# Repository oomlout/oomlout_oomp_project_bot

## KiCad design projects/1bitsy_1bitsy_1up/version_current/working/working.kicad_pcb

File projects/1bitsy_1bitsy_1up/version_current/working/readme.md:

# OOMP Project  
## 1bitsy-1up  by 1Bitsy  
  
oomp key: oomp_projects_flat_1bitsy_1bitsy_1up  
(snippet of original readme)  

This repository contains the board and code used on the 1Bitsy 1UP.  
  
-- Intro  
  
1Bitsy 1UP is a retro inspired handheld game console, the design is based  
around the following __semi arbitrary constraints and requirements.__  
  
* Formfactor: PCB the size of the inside of a GB DMG (the gray one) This will  
  hopefully eventually allow us to put the 1UP pcb inside a modified GB DMG  
  case, either original or new molds sold by several online stores.  
* Main CPU: All code should be able to execute on a 1Bitsy that is fitted with  
  an STM32F415RGT6. That particular chip (due to the package size) does not  
  contain external ram support or LCD display engine. Making LCD drive little  
  bit more tricky. It is a nice constraint that makes coding for the platform  
  bit more of a challenge in the style of classic conloles and 8bit computers  
  because it does not have enough memory for a full framebuffer. ("racing the  
  beam" FTW)  
* Main CPU Mounting: The board contains the 1Bitsy compatible low profile  
  socket using [SL-115-TT-19](https://www.samtec.com/products/sl-115-tt-19)  
  and [BBL-115-T-E](https://www.samtec.com/products/bbl-115-t-e) Samtec  
  connectors as well as one MillMax PogoPin spring loaded SMD connector.  
* LCD: The LCD is a 240x320 TFT display with capacitive touch  
  full source readme at [readme_src.md](readme_src.md)  
  
source repo at: [https://github.com/1Bitsy/1bitsy-1up](https://github.com/1Bitsy/1bitsy-1up)  
## Board  

## Schematic  

[schematic pdf](working_schematic.pdf)  
## Images

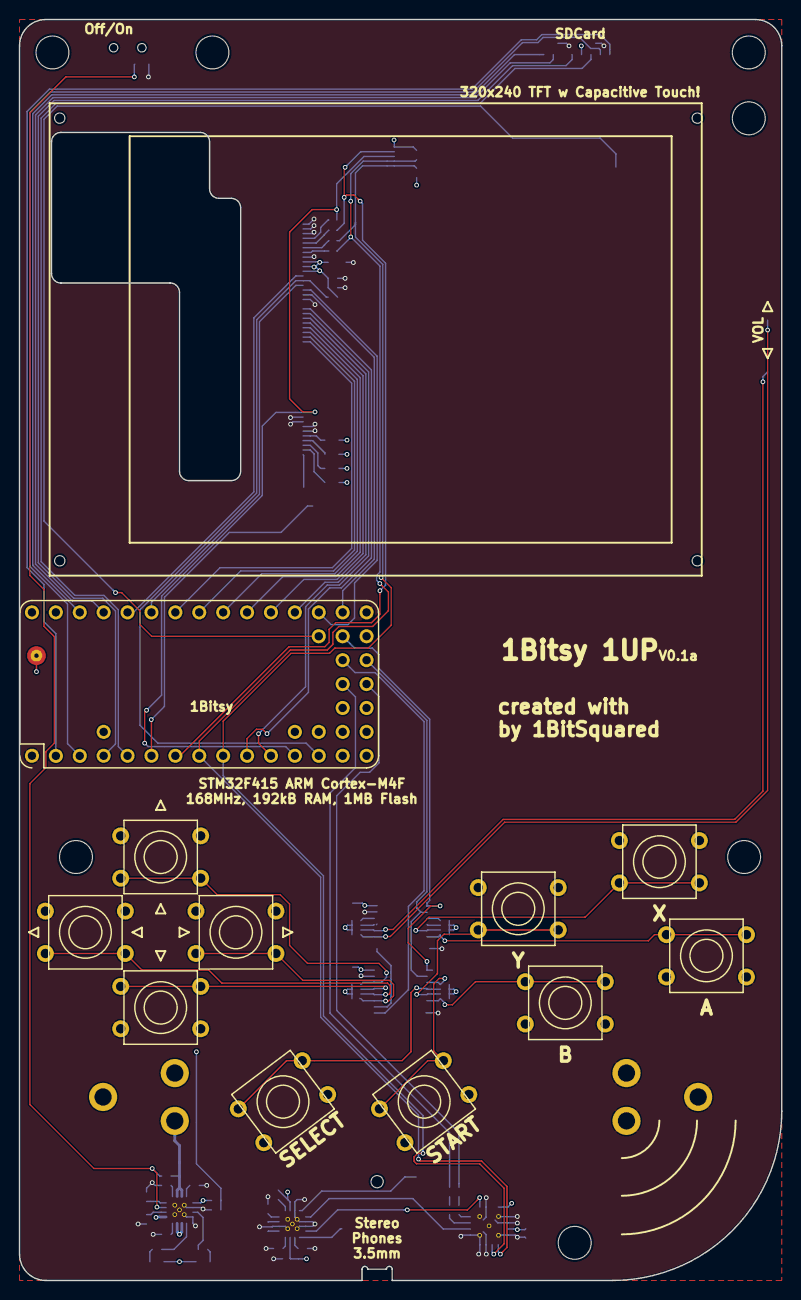
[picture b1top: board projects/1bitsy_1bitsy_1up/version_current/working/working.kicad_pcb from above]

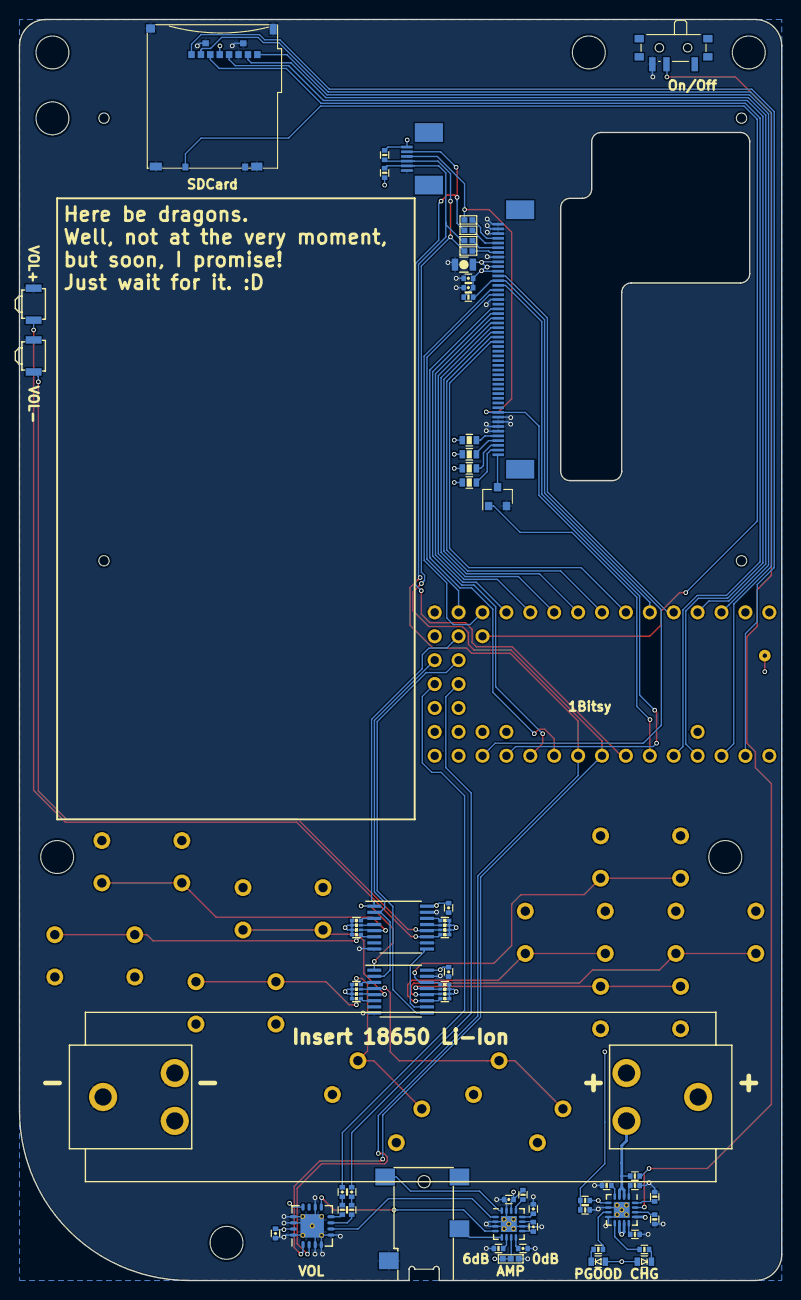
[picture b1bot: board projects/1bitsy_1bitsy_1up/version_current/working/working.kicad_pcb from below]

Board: 4 copper layers, 81.0 x 134.0 mm, 70 parts (58 on the bottom side), 86 nets.

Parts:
BT1: Battery_Cell; BATTERY_CLIP_18650
C1: 10u; C_0805
C2, C3, C10, C11, C12: 100n; C_0402
C4, C5, C6, C7, C9: 1u; C_0402
C8: 2u2; C_0402
CON1: pkl_Micro_SD; SCHA4B0419
D1: YEL; D_0603
D2: GRN; D_0603
J1, J2, J3, J4: pkl_jumper; J_0402
J6: Jumper_Dual; J_0602
J7: pkl_JACK_3C1S; SJ2-35853B-SMT
P1: PogoPin; PAD_MILL-MAX_0906
Q1: NMOS; SOT-23
R1, R2, R3, R4: 10E; R_0603
R5, R8, R9, R12, R13, R16, R17, R21, R22, R23, R25: 10k; R_0402
R6, R7, R10, R11: 10k; R_Array_Convex_4x0402
R14, R15: 50E; R_0402
R18: 0E; R_0402
R19: 590E; R_0402
R20: 1k1; R_0402
R24: 4k7; R_0402
SW1: UP; Tact_Switch_Top_TH_7.8MM_Snap
SW2: Y; Tact_Switch_Top_TH_7.8MM_Snap
SW3: LEFT; Tact_Switch_Top_TH_7.8MM_Snap
SW4: RIGHT; Tact_Switch_Top_TH_7.8MM_Snap
SW5: X; Tact_Switch_Top_TH_7.8MM_Snap
SW6: A; Tact_Switch_Top_TH_7.8MM_Snap
SW7: SELECT; Tact_Switch_Top_TH_7.8MM_Snap
SW8: DOWN; Tact_Switch_Top_TH_7.8MM_Snap
SW9: B; Tact_Switch_Top_TH_7.8MM_Snap
SW10: START; Tact_Switch_Top_TH_7.8MM_Snap
SW11: pkl_SWITCH-SPDT; SW_SPDT_PCM12
SW12, SW13: Tact_Switch_Side_B3U-3000P
U1: 1bitsy-complete-concise; 1bitsy-sl-1xx-xx-19
U2: lcd_50pin_logic; ER-CON50HT
U3: lcd_cap_touch_buydisplay; ER-CON06HB
U4, U5: 74HC165; TSSOP-16_4.4x5mm_Pitch0.65mm
U6: BQ24075; QFN-16-1EP_3x3mm_Pitch0.5mm
U7: TPA6135A2; QFN-16-1EP_3x3mm_Pitch0.5mm
U8: MCP4661-103E/ML; QFN-16-1EP_4x4mm_Pitch0.65mm

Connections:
+3V3: C1.2, C2.2, C3.2, C7.2, C10.2, C11.2, C12.2, CON1.4, J6.2, J6.3, R1.2, R2.2, R3.2, R4.2, R5.1, R6.2, R6.4, R6.6, R6.8, R7.2, R7.4, R7.6, R7.8, R8.1, R9.1, R10.2, R10.4, R10.6, R10.8, R11.2, R11.4, R11.6, R11.8, R13.1, U1.15, U1.29, U2.40, U2.41, U2.42, U3.6, U4.16, U5.16, U7.7, U7.14, U8.12, U8.15
+5V: D1.A, D2.A, R24.1, U1.30, U6.5, U6.10, U6.11
+BATT: BT1.1, R12.1, U1.14, U6.2, U6.3
/AL_AMP: J7.2, U7.16
/AL_ATT: U7.1, U8.6
/AR_AMP: J7.3, U7.5
/AR_ATT: U7.4, U8.9
/AUDIO_L: C4.1, U1.35
/AUDIO_R: C5.1, U1.36
/BA: R10.1, SW6.1, U5.6
/BB: R6.1, SW9.1, U4.6
/BCLK: U1.38, U4.2, U5.2
/BDAT: U1.37, U4.9
/BDOWN: R7.3, SW8.1, U4.13
/BLATCH: U1.39, U4.1, U5.1
/BLEFT: R7.5, SW3.1, U4.12
/BRIGHT: R7.7, SW4.1, U4.11
/BSELECT: R6.5, SW7.1, U4.4
/BSTART: R6.7, SW10.1, U4.3
/BUP: R7.1, SW1.1, U4.14
/BVol+: R11.7, SW12.1, U5.11
/BVol-: R11.5, SW13.1, U5.12
/BX: R10.3, SW5.1, U5.5
/BY: R6.3, SW2.1, U4.5
/LCD_BACK_LIGHT: Q1.1, U1.6
/LCD_BL: Q1.3, U2.1
/LCD_C/D: U1.25, U2.37
/LCD_CS: R5.2, U1.13, U2.38
/LCD_D0: U1.10, U2.32
/LCD_D1: U1.11, U2.31
/LCD_D2: U1.19, U2.30
/LCD_D3: U1.20, U2.29
/LCD_D4: U1.21, U2.28
/LCD_D5: U1.22, U2.27
/LCD_D6: U1.23, U2.26
/LCD_D7: U1.24, U2.25
/LCD_RD: U1.17, U2.35
/LCD_RST: J4.1, U1.12, U2.10, U3.4
/LCD_TE: U1.26, U2.39
/LCD_TOUCH_IRQ: J3.1, U1.7, U3.5
/LCD_WR: U1.18, U2.36
/LED1A: R1.1, U2.2
/LED2A: R2.1, U2.3
/LED3A: R3.1, U2.4
/LED4A: R4.1, U2.5
/SDIO_CD: CON1.9, U1.44
/SDIO_CK: CON1.5, U1.4
/SDIO_CMD: CON1.3, U1.5
/SDIO_D0: CON1.7, U1.27
/SDIO_D1: CON1.8, U1.28
/SDIO_D2: CON1.1, U1.2
/SDIO_D3: CON1.2, U1.3
/SYSOFF: R12.2, SW11.2, U6.15
/USB_V+: P1.1, U6.13
/VOL/TOUCH_SCL: J1.1, R9.2, U1.8, U3.3, U8.1
/VOL/TOUCH_SDA: J2.1, R8.2, U1.9, U3.2, U8.2
/V_BATT: R24.2, R25.1, U1.43
/~CHG: R16.2, U6.9
/~PGOOD: R21.2, U6.7
GND: BT1.2, C1.1, C2.1, C3.1, C7.1, C8.1, C9.1, C10.1, C11.1, C12.1, CON1.6, CON1.10, CON1.11, J6.1, J7.1, Q1.2, R17.2, R18.2, R19.2, R20.2, R22.2, R23.2, R25.2, SW1.2, SW2.2, SW3.2, SW4.2, SW5.2, SW6.2, SW7.2, SW8.2, SW9.2, SW10.2, SW11.3, SW12.2, SW13.2, U1.1, U1.16, U2.6, U2.7, U2.8, U2.9, U2.34, U2.43, U2.48, U2.49, U2.50, U3.1, U4.8, U4.15, U5.8, U5.10, U5.15, U6.6, U6.8, U6.17, U7.2, U7.3, U7.10, U7.15, U7.17, U8.3, U8.4, U8.5, U8.10, U8.13, U8.14, U8.16, U8.17
unnamed: C4.2, R14.2
unnamed: C5.2, R15.2
unnamed: C6.1, U7.9
unnamed: C6.2, U7.11
unnamed: C8.2, U7.12
unnamed: C9.2, U7.8
unnamed: D1.C, R16.1
unnamed: D2.C, R21.1
unnamed: J1.2, U2.44
unnamed: J2.2, U2.45
unnamed: J3.2, U2.46
unnamed: J4.2, U2.47
unnamed: R10.5, U5.4
unnamed: R10.7, U5.3
unnamed: R11.1, U5.14
unnamed: R11.3, U5.13
unnamed: R13.2, U7.13
unnamed: R14.1, U8.7
unnamed: R15.1, U8.8
unnamed: R17.1, U6.1
unnamed: R18.1, U6.14
unnamed: R19.1, U6.16
unnamed: R20.1, U6.12
unnamed: R22.1, U6.4
unnamed: R23.1, U7.6
unnamed: U4.10, U5.9

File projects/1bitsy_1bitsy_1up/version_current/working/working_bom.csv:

"Id";"Designator";"Footprint";"Quantity";"Designation";"Supplier and ref";
1;"R25,R5,R8,R9,R12,R13,R16,R17,R21,R22,R23";"R_0402";11;"10k";;;
2;"R24";"R_0402";1;"4k7";;;
3;"REF**,REF**,REF**,REF**,REF**,REF**,REF**";"MountingHole_3-5mm";7;"MountingHole_3-5mm";;;
4;"P1";"PAD_MILL-MAX_0906";1;"PogoPin";;;
5;"J6";"J_0602";1;"Jumper_Dual";;;
6;"U5,U4";"TSSOP-16_4.4x5mm_Pitch0.65mm";2;"74HC165";;;
7;"U1";"1bitsy-sl-1xx-xx-19";1;"1bitsy-complete-concise";;;
8;"C2,C3,C10,C11,C12";"C_0402";5;"100n";;;
9;"C4,C5,C6,C7,C9";"C_0402";5;"1u";;;
10;"C8";"C_0402";1;"2u2";;;
11;"D1";"D_0603";1;"YEL";;;
12;"D2";"D_0603";1;"GRN";;;
13;"J1,J2,J3,J4";"J_0402";4;"pkl_jumper";;;
14;"Q1";"SOT-23";1;"NMOS";;;
15;"R1,R2,R3,R4";"R_0603";4;"10E";;;
16;"R6,R7,R10,R11";"R_Array_Convex_4x0402";4;"10k";;;
17;"R14,R15";"R_0402";2;"50E";;;
18;"R18";"R_0402";1;"0E";;;
19;"R19";"R_0402";1;"590E";;;
20;"R20";"R_0402";1;"1k1";;;
21;"SW1";"Tact_Switch_Top_TH_7.8MM_Snap";1;"UP";;;
22;"SW2";"Tact_Switch_Top_TH_7.8MM_Snap";1;"Y";;;
23;"SW3";"Tact_Switch_Top_TH_7.8MM_Snap";1;"LEFT";;;
24;"SW4";"Tact_Switch_Top_TH_7.8MM_Snap";1;"RIGHT";;;
25;"SW5";"Tact_Switch_Top_TH_7.8MM_Snap";1;"X";;;
26;"SW6";"Tact_Switch_Top_TH_7.8MM_Snap";1;"A";;;
27;"SW7";"Tact_Switch_Top_TH_7.8MM_Snap";1;"SELECT";;;
28;"SW8";"Tact_Switch_Top_TH_7.8MM_Snap";1;"DOWN";;;
29;"SW9";"Tact_Switch_Top_TH_7.8MM_Snap";1;"B";;;
30;"SW10";"Tact_Switch_Top_TH_7.8MM_Snap";1;"START";;;
31;"SW11";"SW_SPDT_PCM12";1;"pkl_SWITCH-SPDT";;;
32;"SW12,SW13";"Tact_Switch_Side_B3U-3000P";2;"~";;;
33;"U2";"ER-CON50HT";1;"lcd_50pin_logic";;;
34;"U3";"ER-CON06HB";1;"lcd_cap_touch_buydisplay";;;
35;"REF**";"ER-TFT028-4-mechanical";1;"ER-TFT028-4-mechanical";;;
36;"CON1";"SCHA4B0419";1;"pkl_Micro_SD";;;
37;"BT1";"BATTERY_CLIP_18650";1;"Battery_Cell";;;
38;"J7";"SJ2-35853B-SMT";1;"pkl_JACK_3C1S";;;
39;"U7";"QFN-16-1EP_3x3mm_Pitch0.5mm";1;"TPA6135A2";;;
40;"U6";"QFN-16-1EP_3x3mm_Pitch0.5mm";1;"BQ24075";;;
41;"U8";"QFN-16-1EP_4x4mm_Pitch0.65mm";1;"MCP4661-103E/ML";;;
42;"C1";"C_0805";1;"10u";;;

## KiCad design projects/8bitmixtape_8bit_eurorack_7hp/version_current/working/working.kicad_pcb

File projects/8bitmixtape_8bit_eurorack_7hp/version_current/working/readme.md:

# OOMP Project  
## 8Bit_EuroRack-7hp  by 8BitMixtape  
  
oomp key: oomp_projects_flat_8bitmixtape_8bit_eurorack_7hp  
(snippet of original readme)  
  
- 8Bit_EuroRack-7hp  
8Bit Mixtape goes Modular!! Due to popular requests... adapted and improved the mixtape circuit to fit into standard Eurorack Modular format  
  
Join and follow our discussion on the forum:  
  
https://8bitmixtape.discourse.group/t/eurorack-rebooted/47/4  
  
- Features  
  
-- 7hp more space for style!  
  
-- Two board design  
  
Maybe the Eurorack scene like to have more this kinda standard double-decker style  
  
-- 0.1 Prototype - WORKING  

--- to improve  
  
* Put 2 Neopixel und the potentiometers each  
* switch position of Chip and Buttons to create more space between pot and buttons  
* optimize position of jacks and pots (sub-millimeter improvements)  
* What kinda buttons to use????  
* create nice front plates  
* anything else?  
  
-- Schematic  
  
  full source readme at [readme_src.md](readme_src.md)  
  
source repo at: [https://github.com/8BitMixtape/8Bit_EuroRack-7hp](https://github.com/8BitMixtape/8Bit_EuroRack-7hp)  
## Board  

## Schematic  

[schematic pdf](working_schematic.pdf)  
## Images

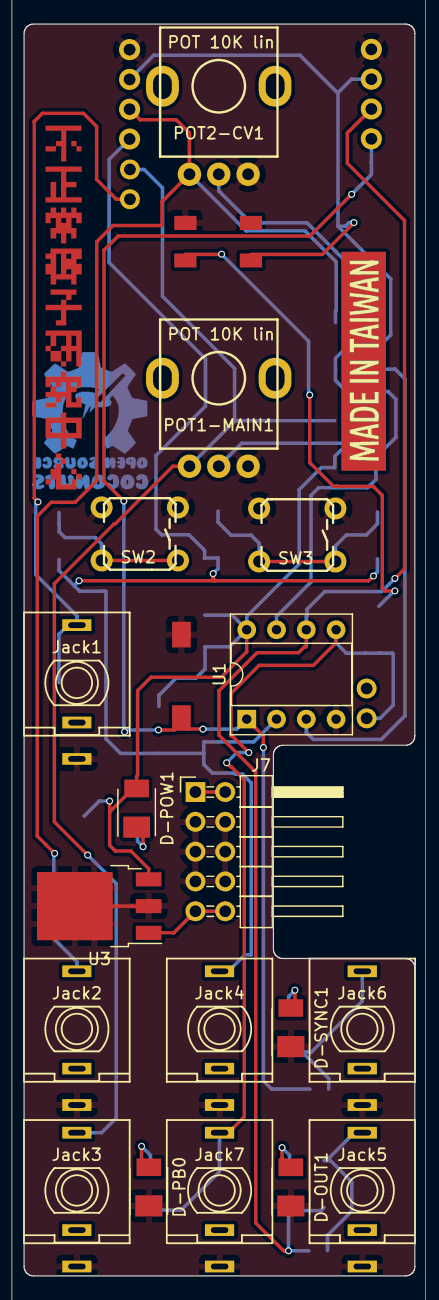
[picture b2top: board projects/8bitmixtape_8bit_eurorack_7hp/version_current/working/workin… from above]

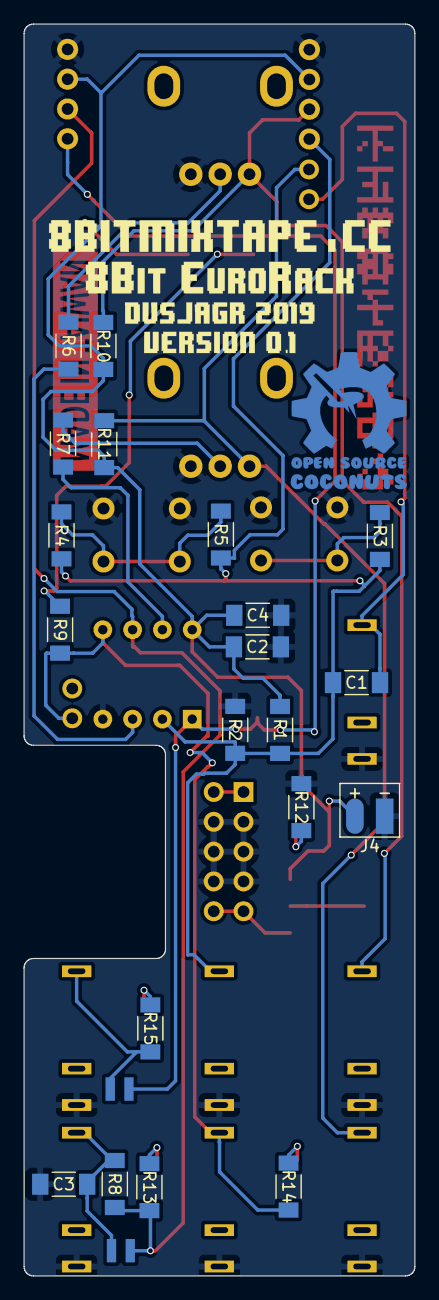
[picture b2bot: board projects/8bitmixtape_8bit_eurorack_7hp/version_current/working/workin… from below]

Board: 2 copper layers, 33.3 x 106.7 mm, 51 parts (26 on the bottom side), 24 nets.

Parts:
C1, C2, C3: 100nF; C_1206_3d
C4: 10uF; C_1206_3d
D1: SK6812; Mixtape_NEO_WS2812B_3d
D-OUT1: LED; LED_PLCC_2835_Handsoldering
D-PB0: LED; LED_PLCC_2835_Handsoldering
D-POW1: LED; LED_PLCC_2835_Handsoldering
D-SYNC1: LED; LED_PLCC_2835_Handsoldering
J1, J2: CONN_01X04; Angled_1x04_Pitch2.54mm-3d
J4: Con_3-5V; Bat_connector_SMD
J5: Conn_01x02; Socket_Strip_Angled_1x02_Pitch2.54mm
J6, J9: Sync_Jumper; Sync_jumper_small
J7: Conn_02x05_Odd_Even; Pin_Header_Angled_2x05_Pitch2.54mm_with_space_for_con
J8: Conn_01x02; Pin_Header_Angled_1x02_Pitch2.54mm
Jack1, Jack2, Jack3, Jack4, Jack5, Jack6, Jack7: JACK_2P; PJ301M-12_dusjagr_3d
POT1-MAIN1, POT2-CV1: POT 10K lin; RD901F-ALPHA-3D
R1, R2, R3, R4, R5: 22k; R_1206_3d
R6, R7: 22K; R_1206_3d
R8, R9: 330; R_1206_3d
R10, R11: 4.7K; R_1206_3d
R12, R13, R14, R15: 1K; R_1206_3d
Ref**: Val**; MadeInTaiwan
Ref**#2: Val**; CACR_chinese_vert
Ref**#3: Val**; Coconut_logo
Ref**#4: Val**; 8bitmixtape_credits_FSilk
SW2, SW3: SW_Push; TACTILE-PTH_3d
SW4: SW_Push; SW_SPST_3d
U1: ATTINY85-20SU; DIP-8_Attiny_with_Socket_3d
U3: 7805; TO-252-3_TabPin2
board1: SVG2SHENZHEN; 8Bit_EuroRack-NEO_7hp

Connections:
+3V3: C2.1, C4.1, D1.3, D-POW1.2, J1.3, J2.2, J4.2, R1.1, R10.1, R11.1, U1.8, U3.3
AudioProg: C1.1, J5.1, Jack1.1
But-L: R3.2, SW2.1
But-R: R4.2, R5.2, SW3.1
CV1_IN: J1.2, Jack2.1, POT2-CV1.1, R10.2
CV2_IN: J5.2, Jack3.1, POT1-MAIN1.1, R11.2
CV_OUT: C3.1, J9.2, Jack5.1, R8.1
DC_in: J7.9, J7.10, U3.1
GND: C2.2, C3.2, C4.2, D1.1, D-OUT1.1, D-PB0.1, D-SYNC1.1, J1.4, J2.1, J4.1, J7.3, J7.4, J7.5, J7.6, J7.7, J7.8, Jack1.3, Jack2.3, Jack3.3, Jack4.3, Jack5.3, Jack6.3, Jack7.3, POT1-MAIN1.3, POT2-CV1.3, R2.2, R12.2, SW2.2, SW3.2, SW4.2, U1.4, U3.2
unnamed: D1.2, R9.1
unnamed: D-OUT1.2, R13.2
unnamed: D-PB0.2, R14.2
unnamed: D-POW1.1, R12.1
unnamed: D-SYNC1.2, R15.2
unnamed: J7.1, J7.2
unnamed: POT1-MAIN1.2, R7.2
unnamed: POT2-CV1.2, R6.2
PB0: J8.1, Jack7.1, R9.2, R14.1, U1.5
PB1: J2.3, J9.1, R8.2, R13.1, U1.6
PB2/A1: R7.1, U1.7
PB4/A2: R6.1, U1.3
PB5: J2.4, J6.1, SW4.1, U1.1
Sync_IN: C1.2, J1.1, Jack4.1, R1.2, R2.1, R3.1, R4.1, R5.1, U1.2
Sync_OUT: J6.2, Jack6.1, R15.1

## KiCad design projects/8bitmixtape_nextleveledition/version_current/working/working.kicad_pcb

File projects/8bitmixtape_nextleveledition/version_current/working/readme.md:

# NextLevelEdition by 8BitMixtape  
This is a harvested standardized copy of a project from github.  
The original project can be found at:  
https://github.com/8BitMixtape/NextLevelEdition  
Please consult that link for additional, details, files, and license information.  
Note: It was auto harvested and if the original repo had more than one board file or anything out of the ordinary the files here are likely not representative.

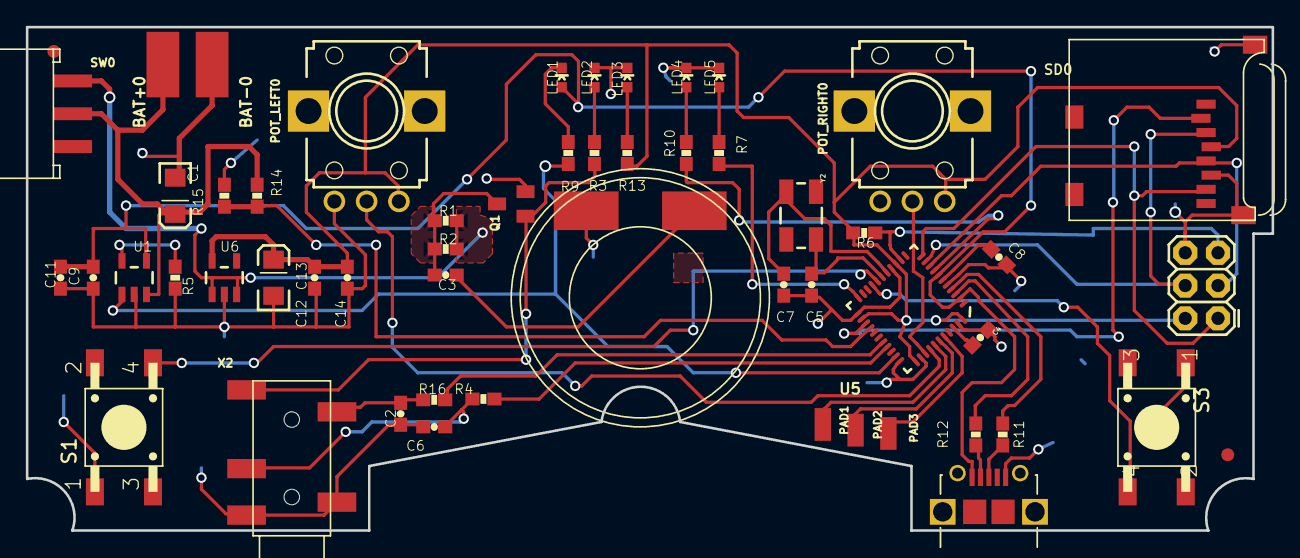
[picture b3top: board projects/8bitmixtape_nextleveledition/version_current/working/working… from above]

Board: 4 copper layers, 96.5 x 39.0 mm, 57 parts (1 on the bottom side), 42 nets.

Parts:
BAT+0: SMD2,54-5,08
BAT-0: SMD2,54-5,08
C1, C13: 10uF; EIA3216
C2, C3, C6, C8, C11, C12: 1uF; 0603-CAP
C4, C14: 0.1uF; 0603-CAP
C5, C7: 22pF; 0603-CAP
C9: 4.7uF; 0603-CAP
JP4: AVR_SPI; 2X3
LED1, LED5: Yellow; LED-0603
LED2: Blue; LED-0603
LED3: Green; LED-0603
LED4: Red; LED-0603
LOGO1: OSHW-LOGOL; OSHW-LOGO-L
PAD1, PAD2, PAD3: WIREPADSMD1,27-254; SMD1,27-2,54
POT_LEFT0: EVUF2A; EVUF
POT_RIGHT0: EVUF2A; EVUF
Q1: BSS123; SOT23
R1, R2: 33; 0603-RES
R3, R4, R7, R10, R13, R16: 330; 0603-RES
R5: 2K; 0603-RES
R6: 10K; 0603-RES
R9: 470; 0603-RES
R11, R12: 22; 0603-RES
R14, R15: 10k; 0603-RES
S1: Left; TASTER-9314_SMD
S3: Right; TASTER-9314_SMD
SD0: MICROSD
SPEAKER0: PS603SPK; PS603
SW0: SWITCH_SMD
U1: MCP73831; SOT23-5
U5: ATMEGA32U4; QFN-44-NOPAD_1_1
U6: MIC5219-3.3; SOT23-5
U$1, U$2: FIDUCIAL; FIDUCIAL_1MM
U$4: FIO_LOGOV2; FUNNEL_LOGO_BOTTOM_V2
X1: USB_B_SMD
X2: PJ-327A
Y2: 8MHz; CRYSTAL-SMD-5X3

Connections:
3.3V: C12.1, C13.A, C14.2, JP4.2, POT_LEFT0.3, POT_RIGHT0.3, R6.2, R13.2, SD0.4, U5.14, U5.24, U5.34, U5.44, U6.5
A0: POT_RIGHT0.2, U5.36
A1: POT_LEFT0.2, U5.37
A2: PAD1.1, U5.38
A3: PAD2.1, U5.39
A4: PAD3.1, U5.40
AREF: C4.2, U5.42
CHARGE_STAT: R9.1, U1.1, U5.32
D2: S3.4, U5.19
D3: S1.4, U5.18
D4: SD0.2, U5.25
D9: R16.2, U5.29
D10: R4.2, U5.30
D14: R10.1, U5.8
D+: R11.1, U5.4
D-: R12.1, U5.3
GND: BAT-0.1, C1.C, C2.1, C4.1, C5.2, C6.1, C7.2, C8.1, C9.2, C11.1, C12.2, C13.C, C14.1, JP4.6, LED2.C, LED3.C, LED4.C, LED5.C, POT_LEFT0.1, POT_RIGHT0.1, Q1.2, R5.2, R15.1, S1.1, S3.1, SD0.6, SD0.MT1, SD0.MT2, SPEAKER0.2, U1.2, U5.5, U5.15, U5.23, U5.33, U5.35, U5.43, U6.2, X1.GND, X2.1, X2.5
MISO: JP4.1, SD0.7, U5.11
MOSI: JP4.4, SD0.3, U5.10
unnamed: C3.2, Q1.3, R1.1, R2.1
unnamed: C3.1, SPEAKER0.1
unnamed: C6.2, R4.1, X2.3
unnamed: R11.2, X1.D+
unnamed: LED2.A, R3.1
unnamed: Q1.1, R3.2, X2.4
unnamed: LED1.C, R9.2
unnamed: R5.1, U1.5
unnamed: LED5.A, R7.2
unnamed: C7.1, U5.16, Y2.1
unnamed: C5.1, U5.17, Y2.3
unnamed: LED4.A, R10.2
unnamed: R12.2, X1.D-
unnamed: C2.2, R16.1, X2.2
unnamed: LED3.A, R13.1
RAW: R1.2, R2.2, SW0.S1, U6.1, U6.3
RST: JP4.5, R6.1, U5.13
SCK: JP4.3, SD0.5, U5.9
TXLED: R7.1, U5.22
UCAP: C8.2, U5.6
USB_VCC: C9.1, C11.2, LED1.A, U1.4, U5.2, U5.7, X1.VCC
VBATT: BAT+0.1, C1.A, R14.2, SW0.COM, U1.3
VBATT_LVL: R14.1, R15.2, U5.26

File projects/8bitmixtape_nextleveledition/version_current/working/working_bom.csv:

"Id";"Designator";"Footprint";"Quantity";"Designation";"Supplier and ref";
1;"Y2";"CRYSTAL-SMD-5X3";1;"8MHz";;;
2;"X1";"USB_B_SMD";1;"USB_B_SMD";;;
3;"U1";"SOT23-5";1;"MCP73831";;;
4;"R9";"0603-RES";1;"470";;;
5;"C9";"0603-CAP";1;"4.7uF";;;
6;"R1,R2";"0603-RES";2;"33";;;
7;"BAT-0,BAT+0";"SMD2,54-5,08";2;"";;;
8;"C5,C7";"0603-CAP";2;"22pF";;;
9;"SPEAKER0";"PS603";1;"PS603SPK";;;
10;"U6";"SOT23-5";1;"MIC5219-3.3";;;
11;"SD0";"MICROSD";1;"MICROSD";;;
12;"C4,C14";"0603-CAP";2;"0.1uF";;;
13;"U$4";"FUNNEL_LOGO_BOTTOM_V2";1;"FIO_LOGOV2";;;
14;"C12,C8,C11,C2,C3,C6";"0603-CAP";6;"1uF";;;
15;"PAD2,PAD3,PAD1";"SMD1,27-2,54";3;"WIREPADSMD1,27-254";;;
16;"C13,C1";"EIA3216";2;"10uF";;;
17;"POT_LEFT0,POT_RIGHT0";"EVUF";2;"EVUF2A";;;
18;"R7,R3,R4,R10,R16,R13";"0603-RES";6;"330";;;
19;"R14,R15";"0603-RES";2;"10k";;;
20;"R6";"0603-RES";1;"10K";;;
21;"LED3";"LED-0603";1;"Green";;;
22;"U$2,U$1";"FIDUCIAL_1MM";2;"FIDUCIAL";;;
23;"Q1";"SOT23";1;"BSS123";;;
24;"R12,R11";"0603-RES";2;"22";;;
25;"JP4";"2X3";1;"AVR_SPI";;;
26;"X2";"PJ-327A";1;"PJ-327A";;;
27;"SW0";"SWITCH_SMD";1;"SWITCH_SMD";;;
28;"S3";"TASTER-9314_SMD";1;"Right";;;
29;"LED1,LED5";"LED-0603";2;"Yellow";;;
30;"LED4";"LED-0603";1;"Red";;;
31;"R5";"0603-RES";1;"2K";;;
32;"U5";"QFN-44-NOPAD_1_1";1;"ATMEGA32U4";;;
33;"S1";"TASTER-9314_SMD";1;"Left";;;
34;"LED2";"LED-0603";1;"Blue";;;
35;"LOGO1";"OSHW-LOGO-L";1;"OSHW-LOGOL";;;

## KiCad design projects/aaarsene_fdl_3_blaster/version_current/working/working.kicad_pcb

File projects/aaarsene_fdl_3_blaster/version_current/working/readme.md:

# OOMP Project  
## FDL-3-Blaster  by aaarsene  
  
oomp key: oomp_projects_flat_aaarsene_fdl_3_blaster  
(snippet of original readme)  

- FDL-3-Blaster  
  
Welcome to the FDL-3 blaster repository  

-- This project is licensed under the terms of the Creative Commons Non-Commercial Attribution Share Alike 4.0 license  
Print it, tweak it, share it and if you do and give us props. Please don't sell it without Project FDL permission.  
  
<br>  
<br>  
  
- Operating your FDL-3  

-- Settings (Applicable to full auto tail, firmware version 1.05)  

**Speed**<br>  
Value: 0 - 100 : Default: 50<br>  
Speed or power setting used to adjust the velocity the blaster fires darts.<br><br>  
  
**ROF (Rate of Fire)**<br>  
Value: 0 - 100 : Default: 100<br>  
Rate of fire setting to adjust time between each dart fired when in burst or full auto.<br><br>  
  
**Burst**<br>  
Value: 1, 2, 3, F : Default: 1<br>  
Number of darts fired per single trigger pull. F (full auto) will continue firing darts until you release the trigger.<br><br>  
  
**MinSpin (Minimum Spinup)**<br>  
Value: 120 - 500 : Default: 220<br>  
Time in milliseconds for motors to spinup between trigger pull and firing dart when speed set to 0.<br><br>  
  
**MaxSpin (Maximum Spinup)**<br>  
Value: 150 - 500 : Default: 200<br>  
Time in milliseconds for motors to spinup between trigger pull and firing dart when speed set to 100.  
Note: MinSpin and MaxSpin together create a range of spinup time. When speed is set to 50, spinup time is half way between MinSpin and MaxSpin. Eg. MinSpin = 200, MaxSpin = 300, Speed =   
  full source readme at [readme_src.md](readme_src.md)  
  
source repo at: [https://github.com/aaarsene/FDL-3-Blaster](https://github.com/aaarsene/FDL-3-Blaster)  
## Board  

## Schematic  

[schematic pdf](working_schematic.pdf)  
## Images

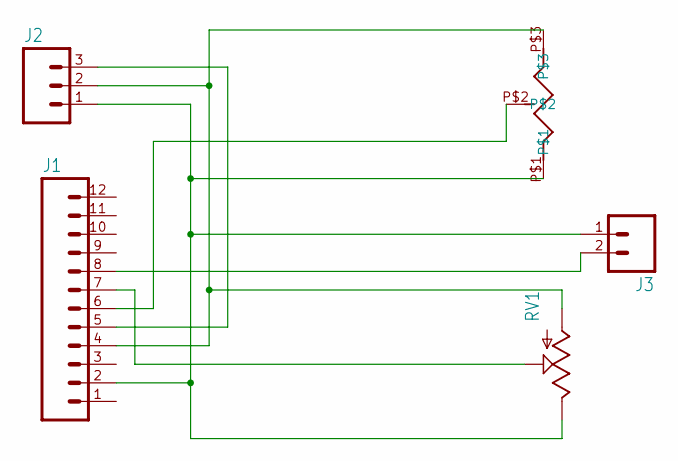
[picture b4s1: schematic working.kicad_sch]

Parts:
J1: M12LONGPADS; 1X12_LONGPADS
J2: M03LONGPADS; 1X03_LONGPADS
J3: M02PTH3; 1X02_LONGPADS
RV1: POTTRIM; TRIM_POT
U$1: THRUHOLEPOT

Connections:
unnamed: J1.4, J2.2, RV1.3 (A), U$1.P$3
unnamed: J1.5, J2.3
unnamed: J1.2, J2.1, J3.1, RV1.2 (E), U$1.P$1
unnamed: J1.6, U$1.P$2
unnamed: J1.7, RV1.1 (S)
unnamed: J1.8, J3.2

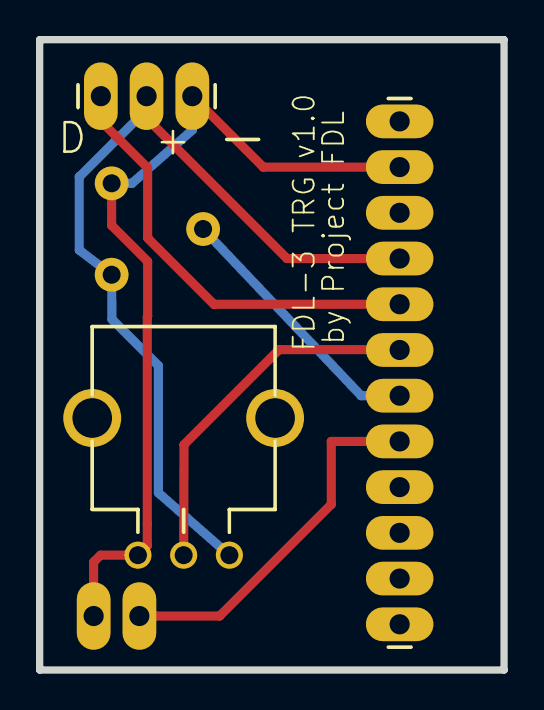
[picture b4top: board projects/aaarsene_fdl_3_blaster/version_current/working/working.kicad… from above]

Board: 2 copper layers, 25.8 x 35.0 mm, 5 parts (0 on the bottom side), 6 nets.

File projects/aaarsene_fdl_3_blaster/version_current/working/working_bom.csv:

"Id";"Designator";"Footprint";"Quantity";"Designation";"Supplier and ref";
1;"J2";"1X03_LONGPADS";1;"";;;
2;"U$1";"THRUHOLEPOT";1;"THRUHOLEPOT";;;
3;"J1";"1X12_LONGPADS";1;"";;;
4;"RV1";"TRIM_POT";1;"";;;
5;"J3";"1X02_LONGPADS";1;"";;;

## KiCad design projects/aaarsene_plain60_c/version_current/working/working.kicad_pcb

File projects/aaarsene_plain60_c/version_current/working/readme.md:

# OOMP Project  
## plain60-c  by aaarsene  
  
oomp key: oomp_projects_flat_aaarsene_plain60_c  
(snippet of original readme)  
  
- Plain60-C rev2.2  

This universal 60% PCB is designed to support as little layouts as possible without limiting usability for most users. The reason I did this is because other PCBs made for this form factor usually have so many supported layouts that it could almost qualify as swiss cheese.  
  
It also features a fuse and an ESD protection chip to protect the MCU and other parts of the PCB.  
  
-- Features  
- Compatible with QMK Firmware and VIA Configurator (if you flash a VIA compatible .hex file)  
- Compatible with most universal 60% cases and HHKB/WKL Tofu by KBDfans  
- USB type-C  
- Optional JST header for connection with daughterboard  
- Footprint for optional speaker (AST1109MLTRQ)  
- ESD protection and fuse  
- No LEDs and no underglow  
- Minimal layout support  
- ISP header  
  
-- Supported layouts  

-- Building  
If you feel like building a few of these PCBs yourself, go to the 'Releases' tab and download the latest gerber files. Order those at your favourite PCB manufacturer, get the components needed (see below) and solder them on! A hot air station is not required but a soldering iron is. Flux is recommended.  
  
-- Opening the project  
To open the files you will need the latest KiCAD nightly version.  
  
-- Bill of materials (BOM)  
Amount is per PCB, multiply as needed.  
  
| LCSC part - | Description   | Value | Package  | Amount |  
| ----------- | ------------- | ----- | -  
  full source readme at [readme_src.md](readme_src.md)  
  
source repo at: [https://github.com/aaarsene/plain60-c](https://github.com/aaarsene/plain60-c)  
## Board  

## Schematic  

[schematic pdf](working_schematic.pdf)  
## Images

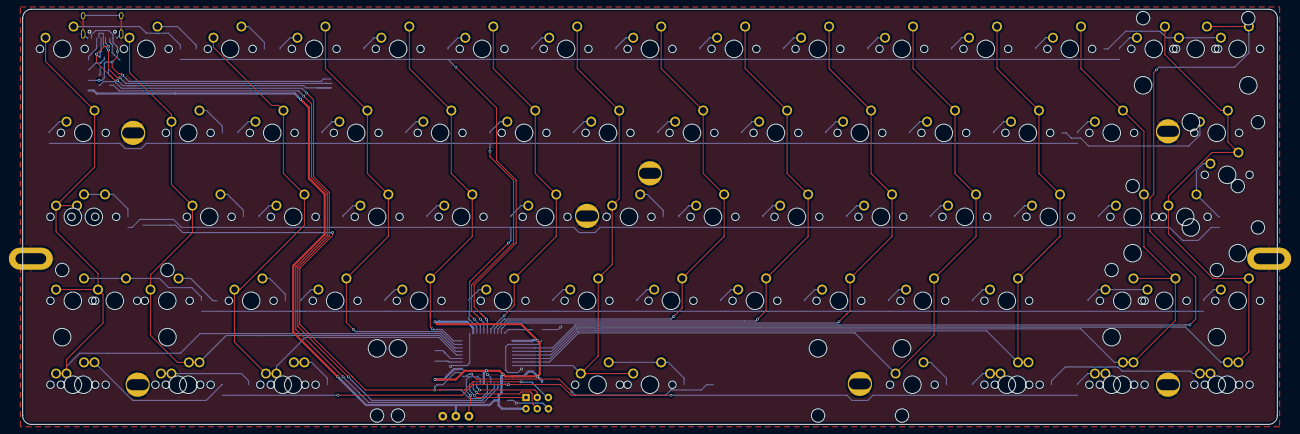
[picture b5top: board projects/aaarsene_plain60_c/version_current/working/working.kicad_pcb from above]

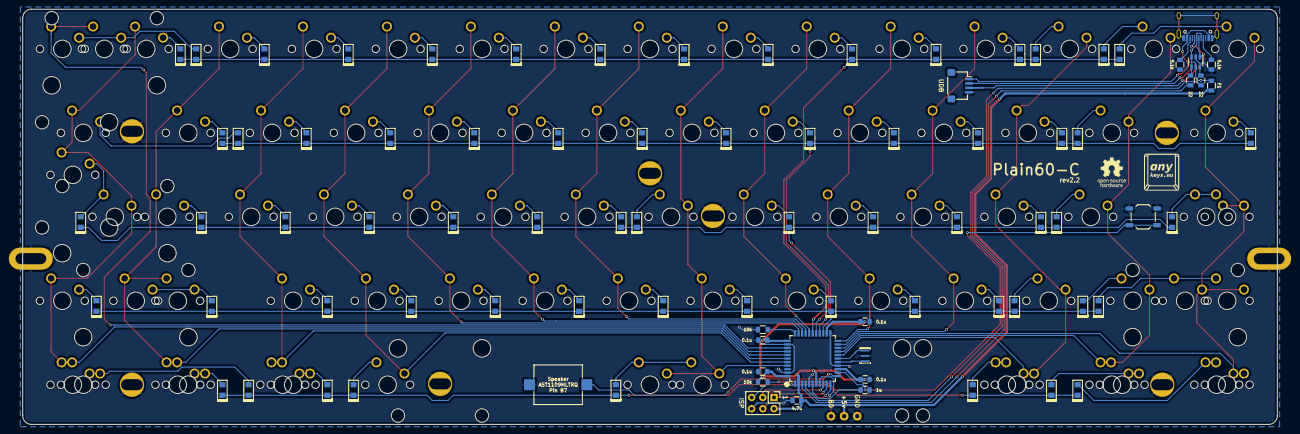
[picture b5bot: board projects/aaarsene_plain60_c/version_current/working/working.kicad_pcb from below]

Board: 2 copper layers, 284.7 x 94.2 mm, 175 parts (89 on the bottom side), 106 nets.

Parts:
C1: 1u; C_0805
C2, C3, C4, C5: 0.1u; C_0805
C6: 4.7u; C_0805
D1, D2, D3, D4, D5, D6, D7, D8, D9, D10, D11, D12, D13, D14, D15, D16, D17, D18, D19, D20, D21, D22, D23, D24, D25, D26, D27, D28, D29, D31, D32, D33, D34, D35, D36, D37, D38, D39, D40, D41, D42, D43, D44, D46, D47, D48, D49, D50, D51, D52, D53, D54, D55, D56, D57, D58, D59, D61, D62, D63, D67, D71, D72, D73, D74: D; D_0805
F1: Polyfuse; R_0805
H1: B0; free_pin
H3: GND; free_pin
H4: +5v; free_pin
J1: HRO-TYPE-C-31-M-12
J2: ISP; isp_standard
J3: ai03_ud; JST_SH_SM04B-SRSS-TB_1x04-1MP_P1.00mm_Horizontal
K1, K2, K3, K4, K5, K6, K7, K8, K9, K10, K11, K12, K13, K14, K15-1, K17, K18, K19, K20, K21, K22, K23, K24, K25, K26, K27, K28, K32, K33, K34, K35, K36, K37, K38, K39, K40, K41, K42, K43, K47, K48, K49, K50, K51, K52, K53, K54, K55, K56, K57, K59, K62-1, K73-1: KEYSW; CHERRY_PLATE_100H
K15: KEYSW; CHERRY_PCB_200H
K16, K29, K61-1, K63-1, K72-1, K74-1: KEYSW; CHERRY_PLATE_150H
K31, K58-1: KEYSW; CHERRY_PLATE_175H
K31-1, K46-1, K61, K62, K63, K71, K72, K73, K74: KEYSW; CHERRY_PLATE_125H
K44, K46: KEYSW; CHERRY_PCB_225H
K44-1: KEYSW; CHERRY_PCB_200H_V
K58: KEYSW; CHERRY_PCB_275H
K67: KEYSW; CHERRY_PCB_625H_F
K67-1: KEYSW; CHERRY_PCB_700H_F
LS1: Speaker; speaker_AST1109MLTRQ
R1, R2: 22; R_0805
R3, R4: 5.1k; R_0805
R5, R6: 10k; R_0805
S1, S2, S3, S6: Screw; 5.5_5x2.5mm
S4, S5: Screw; 10x5_7x2.5mm
S7, S8, S9: Tofu screw; 5.5_5x2.5mm
SW1: SW_PUSH; SW_SPST_TL3342
U1: ATmega32U4; ATMEGA32U4
U2: USBLC6-2SC6
X1: XTAL_GND; Resonator_SMD_muRata_CSTNExxV-3Pin-p1.2

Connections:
D+: J1.6 (DP1), J1.8 (DP2), J3.3, U2.1 (I/O1)
D-: J1.5 (DN2), J1.7 (DN1), J3.2, U2.3 (I/O2)
GND: C1.2, C2.1, C3.1, C4.1, C5.1, C6.1, H3.1, J1.1 (GND), J1.12 (GND), J1.13 (SHIELD), J2.6, J3.4, LS1.2, R3.1, R4.2, R6.1, S1.1, S2.1, S3.1, S4.1, S5.1, S6.1, S7.1, S8.1, S9.1, SW1.1, U1.5 (UGND), U1.15 (GND), U1.23 (GND), U1.35 (GND), U1.43 (GND), U2.2 (GND), X1.3
MISO: J2.1, U1.11 ((PDO/MISO/PCINT3)PB3)
MOSI: J2.4, U1.10 ((PDI/MOSI/PCINT2)PB2)
unnamed: C1.1, U1.6 (UCAP)
unnamed: D1.2 (A), K1.1
unnamed: D2.2 (A), K2.1
unnamed: D3.2 (A), K3.1
unnamed: D4.2 (A), K4.2
unnamed: D5.2 (A), K5.2
unnamed: D6.2 (A), K6.2
unnamed: D7.2 (A), K7.2
unnamed: D8.2 (A), K8.2
unnamed: D9.2 (A), K9.2
unnamed: D10.2 (A), K10.2
unnamed: D11.2 (A), K11.2
unnamed: D12.2 (A), K12.2
unnamed: D13.2 (A), K13.2
unnamed: D14.2 (A), K14.2
unnamed: D15.2 (A), K15.2, K15-1.2
unnamed: D16.2 (A), K16.2
unnamed: D17.2 (A), K17.1
unnamed: D18.2 (A), K18.2
unnamed: D19.2 (A), K19.2
unnamed: D20.2 (A), K20.2
unnamed: D21.2 (A), K21.2
unnamed: D22.2 (A), K22.2
unnamed: D23.2 (A), K23.2
unnamed: D24.2 (A), K24.2
unnamed: D25.2 (A), K25.2
unnamed: D26.2 (A), K26.2
unnamed: D27.2 (A), K27.2
unnamed: D28.2 (A), K28.2
unnamed: D29.2 (A), K29.2
unnamed: D31.2 (A), K31.1, K31-1.1
unnamed: D32.2 (A), K32.1
unnamed: D33.2 (A), K33.2
unnamed: D34.2 (A), K34.2
unnamed: D35.2 (A), K35.2
unnamed: D36.2 (A), K36.2
unnamed: D37.2 (A), K37.1
unnamed: D38.2 (A), K38.2
unnamed: D39.2 (A), K39.2
unnamed: D40.2 (A), K40.2
unnamed: D41.2 (A), K41.2
unnamed: D42.2 (A), K42.2
unnamed: D43.2 (A), K43.2
unnamed: D44.2 (A), K44.1, K44-1.2
unnamed: D46.2 (A), K46.1, K46-1.1
unnamed: D47.2 (A), K47.1
unnamed: D48.2 (A), K48.1
unnamed: D49.2 (A), K49.2
unnamed: D50.2 (A), K50.2
unnamed: D51.2 (A), K51.2
unnamed: D52.2 (A), K52.2
unnamed: D53.2 (A), K53.2
unnamed: D54.2 (A), K54.2
unnamed: D55.2 (A), K55.2
unnamed: D56.2 (A), K56.2
unnamed: D57.2 (A), K57.2
unnamed: D58.2 (A), K58.2, K58-1.2
unnamed: D59.2 (A), K59.2
unnamed: D61.2 (A), K61.1, K61-1.1
unnamed: D62.2 (A), K62.2, K62-1.2
unnamed: D63.2 (A), K63.1, K63-1.1
unnamed: D67.2 (A), K67.1, K67-1.1
unnamed: D71.2 (A), K71.1
unnamed: D72.2 (A), K72.2, K72-1.2
unnamed: D73.2 (A), K73.2, K73-1.2
unnamed: D74.2 (A), K74.2, K74-1.2
unnamed: H1.1, U1.8 ((SS/PCINT0)PB0)
unnamed: J1.4 (CC1), R3.2
unnamed: J1.10 (CC2), R4.1
unnamed: LS1.1, U1.12 ((OC0A/OC1C/~RTS~/PCINT7)PB7)
unnamed: R1.1, U1.4 (D+)
unnamed: R1.2, U2.6 (I/O1)
unnamed: R2.1, U2.4 (I/O2)
unnamed: R2.2, U1.3 (D-)
unnamed: R6.2, U1.33 ((~HWB~)PE2)
unnamed: U1.16 (XTAL2), X1.2
unnamed: U1.17 (XTAL1), X1.1
RST: J2.5, R5.1, SW1.2, U1.13 (RESET)
SCK: J2.3, U1.9 ((SCLK/PCINT1)PB1)
VBUS: F1.2, J1.2 (VBUS), J1.11 (VBUS), J3.1, U2.5 (VBUS)
VCC: C2.2, C3.2, C4.2, C5.2, C6.2, F1.1, H4.1, J2.2, R5.2, U1.2 (UVCC), U1.7 (VBUS), U1.14 (VCC), U1.24 (AVCC), U1.34 (VCC), U1.44 (AVCC)
col0: K1.2, K16.1, K31.2, K31-1.2, K46.2, K46-1.2, K61.2, K61-1.2, U1.20 ((RXD/INT2)PD2)
col1: K2.2, K17.2, K32.2, K47.2, K62.1, K62-1.1, U1.19 ((SDA/INT1)PD1)
col2: K3.2, K18.1, K33.1, K48.2, K63.2, K63-1.2, U1.18 ((OC0B/SCL/INT0)PD0)
col3: K4.1, K19.1, K34.1, K49.1, U1.21 ((TXD/INT3)PD3)
col4: K5.1, K20.1, K35.1, K50.1, U1.22 ((XCK1/~CTS~)PD5)
col5: K6.1, K21.1, K36.1, K51.1, U1.29 ((ADC12/OC1A/~OC4B~/PCINT12)PB5)
col6: K7.1, K22.1, K37.2, K52.1, K67.2, K67-1.2, U1.41 ((ADC0)PF0)
col7: K8.1, K23.1, K38.1, K53.1, U1.30 ((ADC13/OC1B/OC4B/PCINT13)PB6)
col8: K9.1, K24.1, K39.1, K54.1, U1.31 ((OC3A/~OC4A~)PC6)
col9: K10.1, K25.1, K40.1, K55.1, U1.32 ((ICP3/CLK0/OC4A)PC7)
col10: K11.1, K26.1, K41.1, K56.1, K71.2, U1.40 ((ADC1)PF1)
col11: K12.1, K27.1, K42.1, K57.1, K72.1, K72-1.1, U1.39 ((ADC4/TCK)PF4)
col12: K13.1, K28.1, K43.1, K58.1, K58-1.1, K73.1, K73-1.1, U1.38 ((ADC5/TMS)PF5)
col13: K14.1, K29.1, K44.2, K44-1.1, K59.1, K74.1, K74-1.1, U1.37 ((ADC6/TDO)PF6)
col14: K15.1, K15-1.1, U1.36 ((ADC7/TDI)PF7)
row0: D1.1 (K), D2.1 (K), D3.1 (K), D4.1 (K), D5.1 (K), D6.1 (K), D7.1 (K), D8.1 (K), D9.1 (K), D10.1 (K), D11.1 (K), D12.1 (K), D13.1 (K), D14.1 (K), D15.1 (K), U1.28 ((ADC11/PCINT4)PB4)
row1: D16.1 (K), D17.1 (K), D18.1 (K), D19.1 (K), D20.1 (K), D21.1 (K), D22.1 (K), D23.1 (K), D24.1 (K), D25.1 (K), D26.1 (K), D27.1 (K), D28.1 (K), D29.1 (K), U1.27 ((T0/OC4D/ADC10)PD7)
row2: D31.1 (K), D32.1 (K), D33.1 (K), D34.1 (K), D35.1 (K), D36.1 (K), D37.1 (K), D38.1 (K), D39.1 (K), D40.1 (K), D41.1 (K), D42.1 (K), D43.1 (K), D44.1 (K), U1.26 ((T1/~OC4D~/ADC9)PD6)
row3: D46.1 (K), D47.1 (K), D48.1 (K), D49.1 (K), D50.1 (K), D51.1 (K), D52.1 (K), D53.1 (K), D54.1 (K), D55.1 (K), D56.1 (K), D57.1 (K), D58.1 (K), D59.1 (K), U1.25 ((ICP2/ADC8)PD4)
row4: D61.1 (K), D62.1 (K), D63.1 (K), D67.1 (K), D71.1 (K), D72.1 (K), D73.1 (K), D74.1 (K), U1.1 ((INT6/AIN0)PE6)

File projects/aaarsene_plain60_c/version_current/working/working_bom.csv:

"Id";"Designator";"Footprint";"Quantity";"Designation";"Supplier and ref";
1;"K19,K20,K23,K24,K17,K22,K21,K18,K8,K10,K14,K5,K13,K12,K11,K9,K7,K6,K4,K2,K1,K3,K62-1,K53,K57,K54,K56,K52,K55,K15-1,K28,K48,K25,K36,K33,K59,K39,K27,K50,K34,K47,K43,K38,K35,K32,K40,K42,K41,K26,K37,K51,K73-1,K49";"CHERRY_PLATE_100H";53;"KEYSW";;;
2;"K16,K61-1,K29,K63-1,K72-1,K74-1";"CHERRY_PLATE_150H";6;"KEYSW";;;
3;"K15";"CHERRY_PCB_200H";1;"KEYSW";;;
4;"K71,K31-1,K46-1,K74,K73,K63,K72,K61,K62";"CHERRY_PLATE_125H";9;"KEYSW";;;
5;"K58-1,K31";"CHERRY_PLATE_175H";2;"KEYSW";;;
6;"K44,K46";"CHERRY_PCB_225H";2;"KEYSW";;;
7;"S4,S5";"10x5_7x2.5mm";2;"Screw";;;
8;"K58";"CHERRY_PCB_275H";1;"KEYSW";;;
9;"K67";"CHERRY_PCB_625H_F";1;"KEYSW";;;
10;"S8,S7,S9";"5.5_5x2.5mm";3;"Tofu screw";;;
11;"S2,S1,S3,S6";"5.5_5x2.5mm";4;"Screw";;;
12;"K67-1";"CHERRY_PCB_700H_F";1;"KEYSW";;;
13;"K44-1";"CHERRY_PCB_200H_V";1;"KEYSW";;;
14;"D73,D72,D71,D67,D63,D59,D58,D57,D56,D53,D51,D50,D27,D42,D18,D25,D41,D36,D31,D40,D37,D32,D34,D21,D26,D22,D24,D43,D38,D35,D48,D54,D44,D62,D39,D20,D28,D33,D23,D55,D52,D19,D10,D14,D9,D13,D11,D15,D17,D16,D12,D7,D3,D5,D8,D6,D4,D74,D49,D46,D29,D1,D47,D2,D61";"D_0805";65;"D";;;
15;"U1";"ATMEGA32U4";1;"ATmega32U4";;;
16;"X1";"Resonator_SMD_muRata_CSTNExxV-3Pin-p1.2";1;"XTAL_GND";;;
17;"SW1";"SW_SPST_TL3342";1;"SW_PUSH";;;
18;"R6,R5";"R_0805";2;"10k";;;
19;"G***";"oshw";1;"LOGO";;;
20;"H4";"free_pin";1;"+5v";;;
21;"H1";"free_pin";1;"B0";;;
22;"R1,R2";"R_0805";2;"22";;;
23;"J1";"HRO-TYPE-C-31-M-12";1;"HRO-TYPE-C-31-M-12";;;
24;"C4,C5,C2,C3";"C_0805";4;"0.1u";;;
25;"F1";"R_0805";1;"Polyfuse";;;
26;"C1";"C_0805";1;"1u";;;
27;"R4,R3";"R_0805";2;"5.1k";;;
28;"U2";"USBLC6-2SC6";1;"USBLC6-2SC6";;;
29;"H3";"free_pin";1;"GND";;;
30;"J2";"isp_standard";1;"ISP";;;
31;"G***";"logo_new";1;"LOGO";;;
32;"J3";"JST_SH_SM04B-SRSS-TB_1x04-1MP_P1.00mm_Horizontal";1;"ai03_ud";;;
33;"LS1";"speaker_AST1109MLTRQ";1;"Speaker";;;
34;"C6";"C_0805";1;"4.7u";;;

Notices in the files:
projects/1bitsy_1bitsy_1up/version_current/working/working.kicad_pcb:
(C) 2017 Piotr Esden-Tempski
(C) 2017 1BitSquared LLC
License: CC-BY-SA V4.0
